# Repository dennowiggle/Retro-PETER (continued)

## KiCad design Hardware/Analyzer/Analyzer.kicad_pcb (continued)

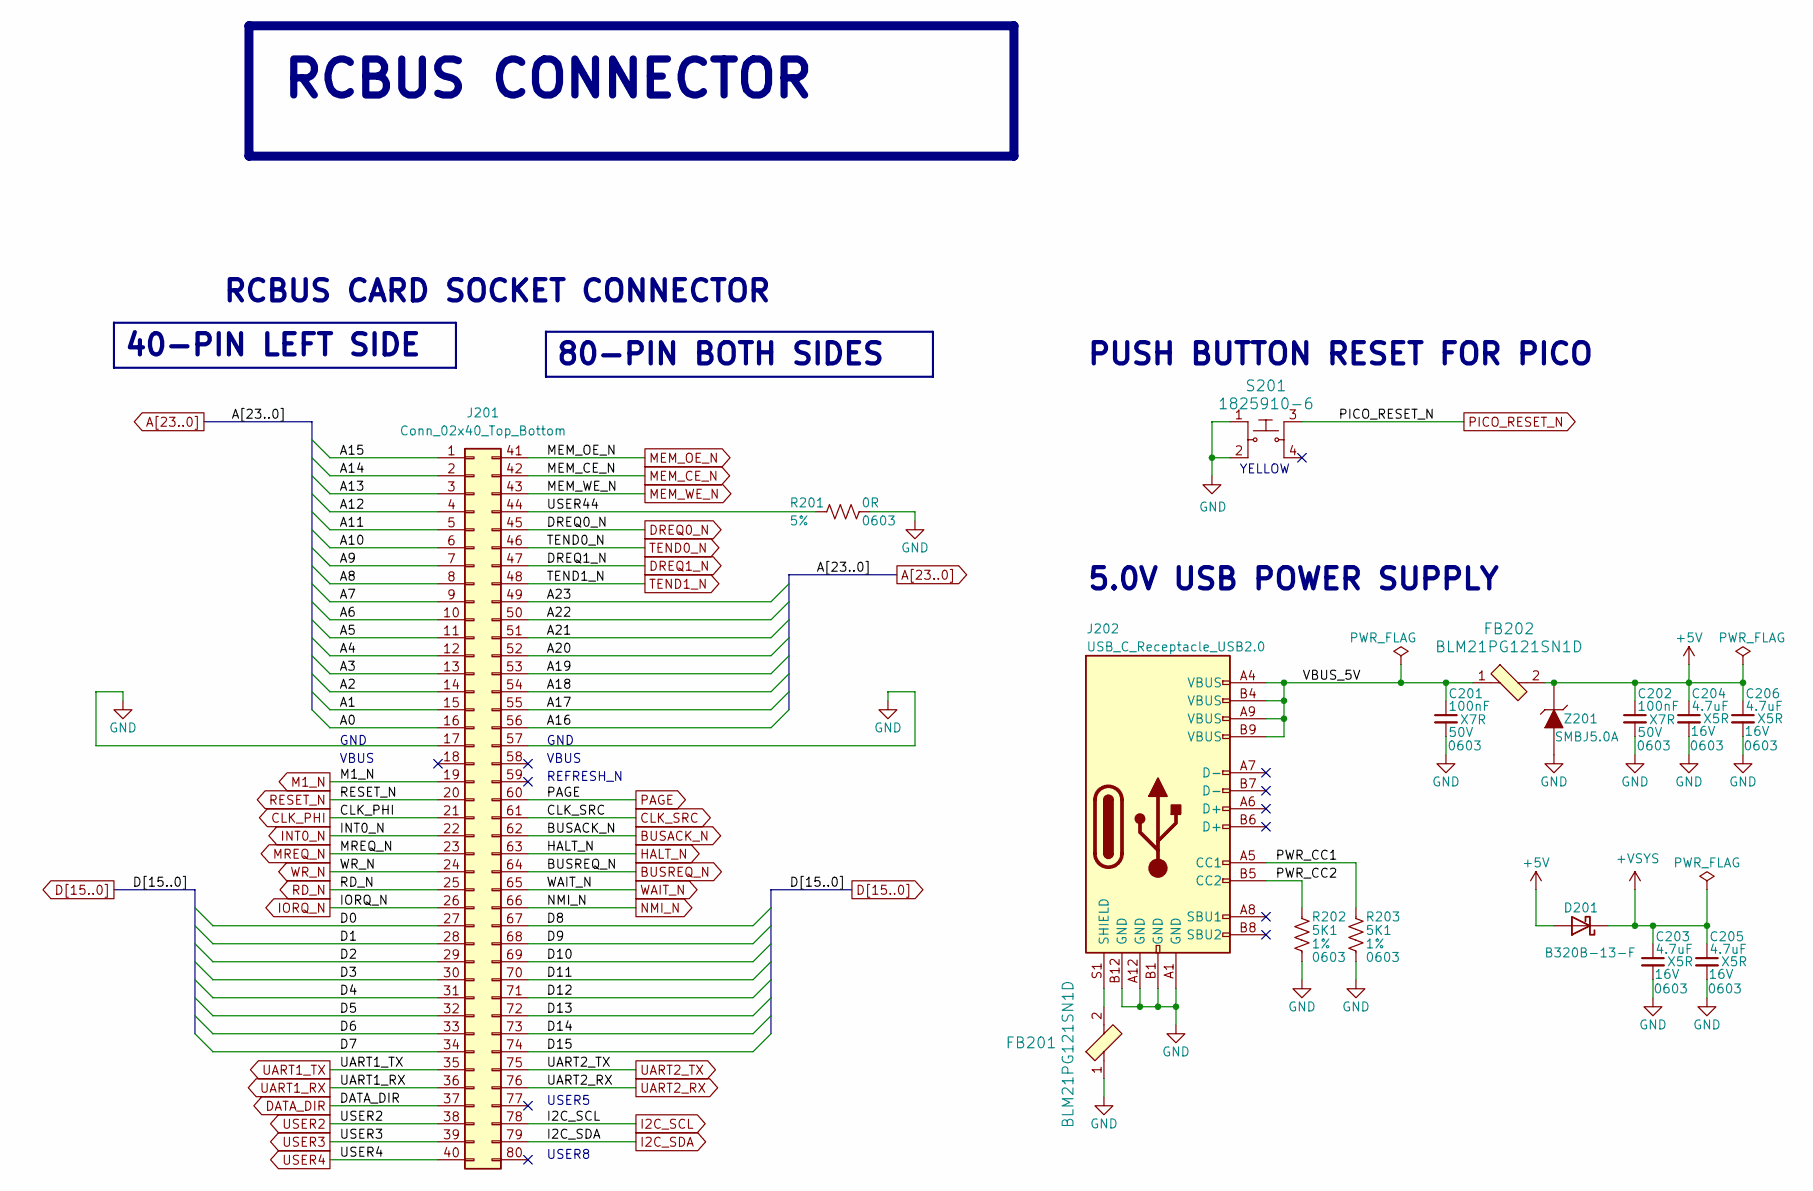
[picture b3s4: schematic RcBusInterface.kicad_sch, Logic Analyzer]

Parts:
C201, C202: 100nF; C_0603_1608Metric; Voltage 50V; Tolerance 10%; MPN CC0603KRX7R9BB104; Digikey 311-1344-1-ND
C203, C204, C205, C206: 4.7uF; C_0603_1608Metric; Voltage 16V; Tolerance 10%; MPN CL10A475KO8NNNC; Digikey 1276-1784-1-ND
D201: B320B-13-F; D_SMB; MPN B320B-13-F; Digikey B320B-FDICT-ND
FB201, FB202: BLM21PG121SN1D; L_0805_2012Metric; MPN BLM21PG121SN1D; Digikey 490-5986-1-ND
J201: Conn_02x40_Top_Bottom; RCBUS_PinHeader_2x40_P2.54mm_Horizontal; MPN PH2RA-80-UA; Digikey 2057-PH2RA-80-UA-ND
J202: USB_C_Receptacle_USB2.0; USB_C_Receptacle_HRO_TYPE-C-31-M-12; MPN USB4105-GF-A; LCSC Part # C167321
R201: 0R; R_0603_1608Metric; Tolerance 5%; MPN RC0603JR-070RL; Digikey 311-0.0GRCT-ND
R202, R203: 5K1; R_0603_1608Metric; Tolerance 1%; MPN RC0603FR-075K1L; Digikey 311-5.10KHRCT-ND
S201: 1825910-6; Switch_Tactile_THT_6x6mm; MPN 1825910-6; Digikey 450-1650-ND
Z201: SMBJ5.0A; D_SMB; MPN SMBJ5.0A; Digikey SMBJ5.0ALFCT-ND

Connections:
+5V: C202.1, C204.1, C206.1, D201.2 (A), FB202.2, Z201.1
+VSYS: C203.1, C205.1, D201.1 (K); also elsewhere on the board
/RcBusInterface/PWR_CC1: J202.A5 (CC1), R203.1
/RcBusInterface/PWR_CC2: J202.B5 (CC2), R202.1
/RcBusInterface/USER44: J201.44, R201.1
/RcBusInterface/VBUS_5V: C201.1, FB202.1, J202.A4 (VBUS), J202.A9 (VBUS), J202.B4 (VBUS), J202.B9 (VBUS)
A0: J201.16; also elsewhere on the board
A1: J201.15; also elsewhere on the board
A2: J201.14; also elsewhere on the board
A3: J201.13; also elsewhere on the board
A4: J201.12; also elsewhere on the board
A5: J201.11; also elsewhere on the board
A6: J201.10; also elsewhere on the board
A7: J201.9; also elsewhere on the board
A8: J201.8; also elsewhere on the board
A9: J201.7; also elsewhere on the board
A10: J201.6; also elsewhere on the board
A11: J201.5; also elsewhere on the board
A12: J201.4; also elsewhere on the board
A13: J201.3; also elsewhere on the board
A14: J201.2; also elsewhere on the board
A15: J201.1; also elsewhere on the board
A16: J201.56; also elsewhere on the board
A17: J201.55; also elsewhere on the board
A18: J201.54; also elsewhere on the board
A19: J201.53; also elsewhere on the board
A20: J201.52; also elsewhere on the board
A21: J201.51; also elsewhere on the board
A22: J201.50; also elsewhere on the board
A23: J201.49; also elsewhere on the board
BUSACK_N: J201.62; also elsewhere on the board
BUSREQ_N: J201.64; also elsewhere on the board
CLK_PHI: J201.21; also elsewhere on the board
CLK_SRC: J201.61; also elsewhere on the board
D0: J201.27; also elsewhere on the board
D1: J201.28; also elsewhere on the board
D2: J201.29; also elsewhere on the board
D3: J201.30; also elsewhere on the board
D4: J201.31; also elsewhere on the board
D5: J201.32; also elsewhere on the board
D6: J201.33; also elsewhere on the board
D7: J201.34; also elsewhere on the board
D8: J201.67; also elsewhere on the board
D9: J201.68; also elsewhere on the board
D10: J201.69; also elsewhere on the board
D11: J201.70; also elsewhere on the board
D12: J201.71; also elsewhere on the board
D13: J201.72; also elsewhere on the board
D14: J201.73; also elsewhere on the board
D15: J201.74; also elsewhere on the board
DATA_DIR: J201.37; also elsewhere on the board
DREQ0_N: J201.45; also elsewhere on the board
DREQ1_N: J201.47; also elsewhere on the board
GND: C201.2, C202.2, C203.2, C204.2, C205.2, C206.2, FB201.1, J201.17, J201.57, J202.A1 (GND), J202.A12 (GND), J202.B1 (GND), J202.B12 (GND), R201.2, R202.2, R203.2, S201.1, S201.2, Z201.2; also elsewhere on the board
HALT_N: J201.63; also elsewhere on the board
I2C_SCL: J201.78; also elsewhere on the board
I2C_SDA: J201.79; also elsewhere on the board
INT0_N: J201.22; also elsewhere on the board
IORQ_N: J201.26; also elsewhere on the board
M1_N: J201.19; also elsewhere on the board
MEM_CE_N: J201.42; also elsewhere on the board
MEM_OE_N: J201.41; also elsewhere on the board
MEM_WE_N: J201.43; also elsewhere on the board
MREQ_N: J201.23; also elsewhere on the board
NMI_N: J201.66; also elsewhere on the board
unnamed: FB201.2, J202.S1 (SHIELD)
PAGE: J201.60; also elsewhere on the board
PICO_RESET_N: S201.3; also elsewhere on the board
RD_N: J201.25; also elsewhere on the board
RESET_N: J201.20; also elsewhere on the board
TEND0_N: J201.46; also elsewhere on the board
TEND1_N: J201.48; also elsewhere on the board
UART1_RX: J201.36; also elsewhere on the board
UART1_TX: J201.35; also elsewhere on the board
UART2_RX: J201.76; also elsewhere on the board
UART2_TX: J201.75; also elsewhere on the board
USER2: J201.38; also elsewhere on the board
USER3: J201.39; also elsewhere on the board
USER4: J201.40; also elsewhere on the board
WAIT_N: J201.65; also elsewhere on the board
WR_N: J201.24; also elsewhere on the board

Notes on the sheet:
5.0V USB POWER SUPPLY
REFRESH_N
VBUS
40-PIN LEFT SIDE
USER8
80-PIN BOTH SIDES
YELLOW
GND
RCBUS CARD SOCKET CONNECTOR
PUSH BUTTON RESET FOR PICO
USER5
RCBUS CONNECTOR

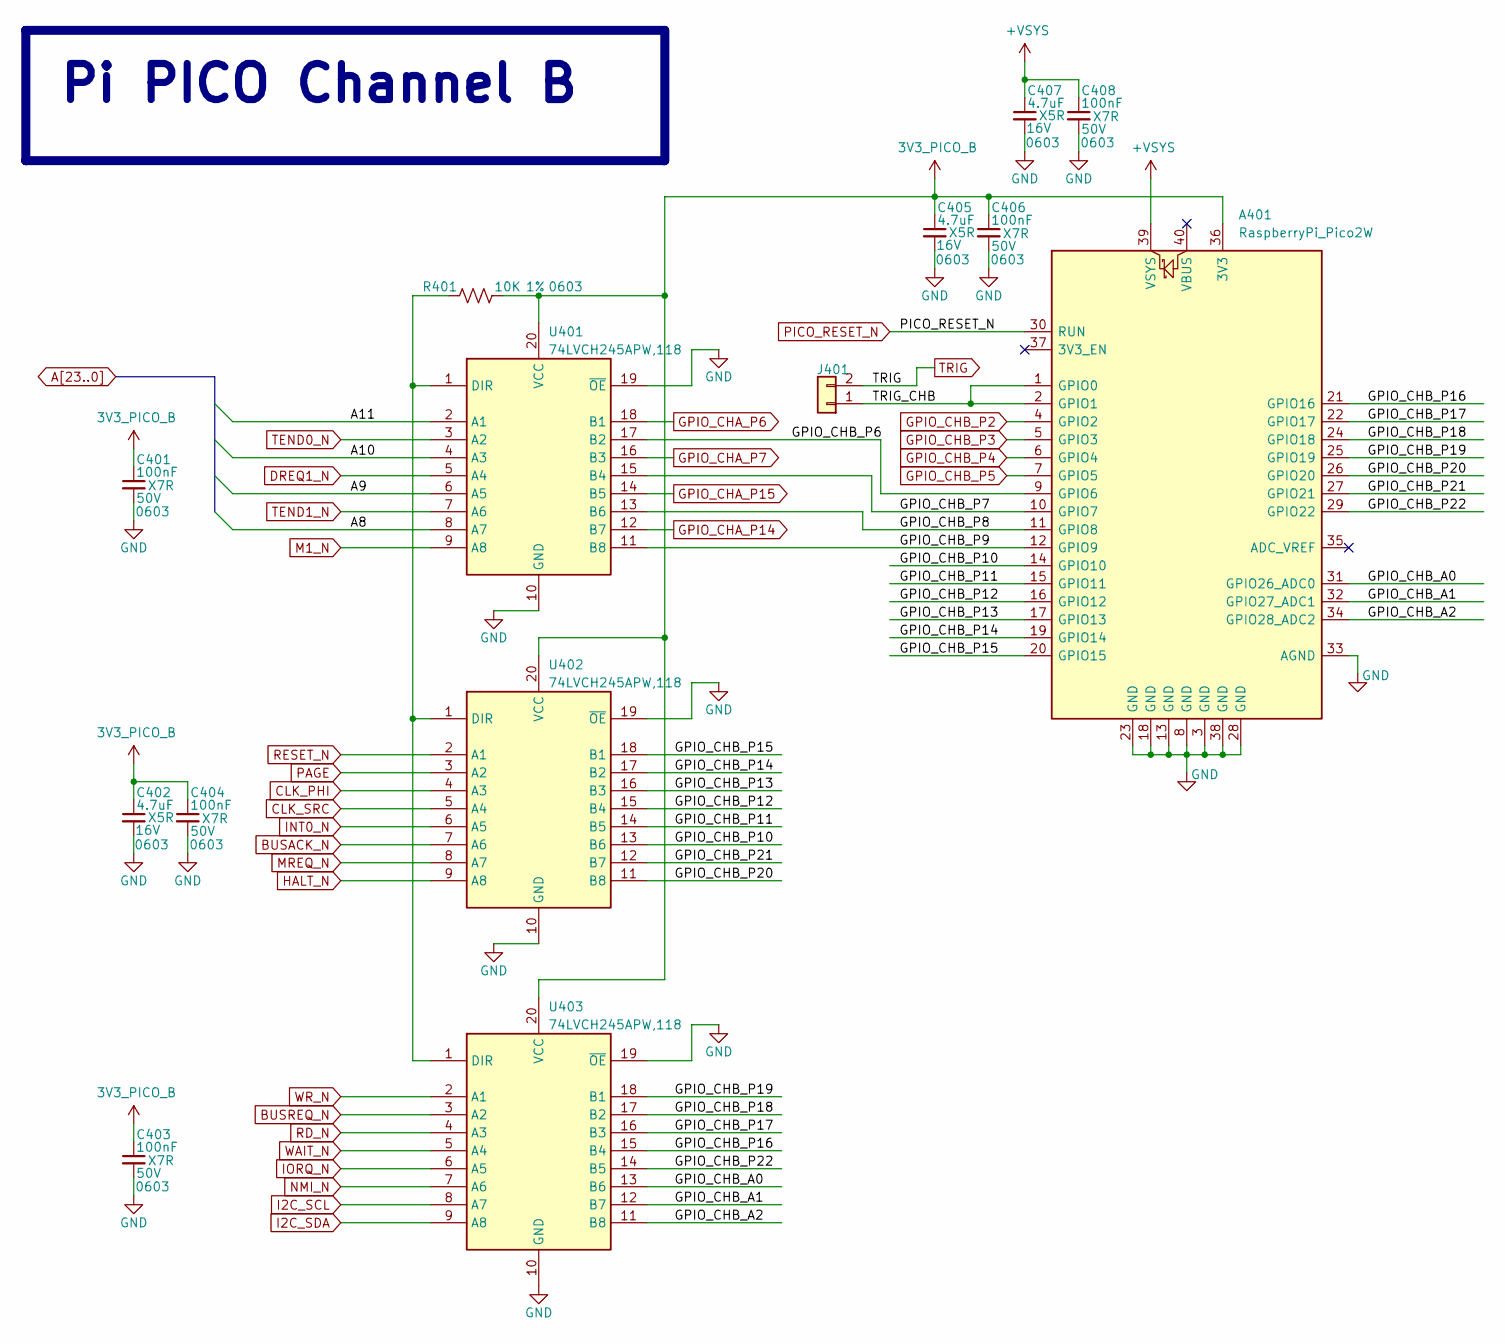
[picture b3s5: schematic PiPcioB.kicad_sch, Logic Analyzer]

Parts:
A401: RaspberryPi_Pico2W; RaspberryPi_Pico_Common_THT; MPN SC1634; Digikey 2648-SC1634-ND
C401, C403, C404, C406, C408: 100nF; C_0603_1608Metric; Voltage 50V; Tolerance 10%; MPN CC0603KRX7R9BB104; Digikey 311-1344-1-ND
C402, C405, C407: 4.7uF; C_0603_1608Metric; Voltage 16V; Tolerance 10%; MPN CL10A475KO8NNNC; Digikey 1276-1784-1-ND
J401: Conn_01x02; PinHeader_1x02_P2.54mm_Vertical; MPN PH2-02-UA; Digikey 2057-PH2-02-UA-ND
R401: 10K; R_0603_1608Metric; Tolerance 1%; MPN RC0603FR-0710KL; Digikey 311-10.0KHRCT-ND
U401, U402, U403: 74LVCH245APW,118; TSSOP-20_4.4x6.5mm_P0.65mm; MPN 74LVCH245APW,118; Digikey 1727-4041-1-ND

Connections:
3V3_PICO_B: A401.36 (3V3), C401.1, C402.1, C403.1, C404.1, C405.1, C406.1, R401.2, U401.20 (VCC), U402.20 (VCC), U403.20 (VCC)
+VSYS: A401.39 (VSYS), C407.1, C408.1; also elsewhere on the board
/PiPicoB/GPIO_CHB_A0: A401.31 (GPIO26_ADC0), U403.13 (B6)
/PiPicoB/GPIO_CHB_A1: A401.32 (GPIO27_ADC1), U403.12 (B7)
/PiPicoB/GPIO_CHB_A2: A401.34 (GPIO28_ADC2), U403.11 (B8)
/PiPicoB/GPIO_CHB_P6: A401.9 (GPIO6), U401.17 (B2)
/PiPicoB/GPIO_CHB_P7: A401.10 (GPIO7), U401.15 (B4)
/PiPicoB/GPIO_CHB_P8: A401.11 (GPIO8), U401.13 (B6)
/PiPicoB/GPIO_CHB_P9: A401.12 (GPIO9), U401.11 (B8)
/PiPicoB/GPIO_CHB_P10: A401.14 (GPIO10), U402.13 (B6)
/PiPicoB/GPIO_CHB_P11: A401.15 (GPIO11), U402.14 (B5)
/PiPicoB/GPIO_CHB_P12: A401.16 (GPIO12), U402.15 (B4)
/PiPicoB/GPIO_CHB_P13: A401.17 (GPIO13), U402.16 (B3)
/PiPicoB/GPIO_CHB_P14: A401.19 (GPIO14), U402.17 (B2)
/PiPicoB/GPIO_CHB_P15: A401.20 (GPIO15), U402.18 (B1)
/PiPicoB/GPIO_CHB_P16: A401.21 (GPIO16), U403.15 (B4)
/PiPicoB/GPIO_CHB_P17: A401.22 (GPIO17), U403.16 (B3)
/PiPicoB/GPIO_CHB_P18: A401.24 (GPIO18), U403.17 (B2)
/PiPicoB/GPIO_CHB_P19: A401.25 (GPIO19), U403.18 (B1)
/PiPicoB/GPIO_CHB_P20: A401.26 (GPIO20), U402.11 (B8)
/PiPicoB/GPIO_CHB_P21: A401.27 (GPIO21), U402.12 (B7)
/PiPicoB/GPIO_CHB_P22: A401.29 (GPIO22), U403.14 (B5)
/PiPicoB/TRIG_CHB: A401.1 (GPIO0), A401.2 (GPIO1), J401.1
A8: U401.8 (A7); also elsewhere on the board
A9: U401.6 (A5); also elsewhere on the board
A10: U401.4 (A3); also elsewhere on the board
A11: U401.2 (A1); also elsewhere on the board
BUSACK_N: U402.7 (A6); also elsewhere on the board
BUSREQ_N: U403.3 (A2); also elsewhere on the board
CLK_PHI: U402.4 (A3); also elsewhere on the board
CLK_SRC: U402.5 (A4); also elsewhere on the board
DREQ1_N: U401.5 (A4); also elsewhere on the board
GND: A401.3 (GND), A401.8 (GND), A401.13 (GND), A401.18 (GND), A401.23 (GND), A401.28 (GND), A401.33 (AGND), A401.38 (GND), C401.2, C402.2, C403.2, C404.2, C405.2, C406.2, C407.2, C408.2, U401.10 (GND), U401.19 (~OE), U402.10 (GND), U402.19 (~OE), U403.10 (GND), U403.19 (~OE); also elsewhere on the board
GPIO_CHA_P6: U401.18 (B1); also elsewhere on the board
GPIO_CHA_P7: U401.16 (B3); also elsewhere on the board
GPIO_CHA_P14: U401.12 (B7); also elsewhere on the board
GPIO_CHA_P15: U401.14 (B5); also elsewhere on the board
GPIO_CHB_P2: A401.4 (GPIO2); also elsewhere on the board
GPIO_CHB_P3: A401.5 (GPIO3); also elsewhere on the board
GPIO_CHB_P4: A401.6 (GPIO4); also elsewhere on the board
GPIO_CHB_P5: A401.7 (GPIO5); also elsewhere on the board
HALT_N: U402.9 (A8); also elsewhere on the board
I2C_SCL: U403.8 (A7); also elsewhere on the board
I2C_SDA: U403.9 (A8); also elsewhere on the board
INT0_N: U402.6 (A5); also elsewhere on the board
IORQ_N: U403.6 (A5); also elsewhere on the board
M1_N: U401.9 (A8); also elsewhere on the board
MREQ_N: U402.8 (A7); also elsewhere on the board
NMI_N: U403.7 (A6); also elsewhere on the board
unnamed: R401.1, U401.1 (DIR), U402.1 (DIR), U403.1 (DIR)
PAGE: U402.3 (A2); also elsewhere on the board
PICO_RESET_N: A401.30 (RUN); also elsewhere on the board
RD_N: U403.4 (A3); also elsewhere on the board
RESET_N: U402.2 (A1); also elsewhere on the board
TEND0_N: U401.3 (A2); also elsewhere on the board
TEND1_N: U401.7 (A6); also elsewhere on the board
TRIG: J401.2; also elsewhere on the board
WAIT_N: U403.5 (A4); also elsewhere on the board
WR_N: U403.2 (A1); also elsewhere on the board

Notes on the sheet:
Pi PICO Channel B

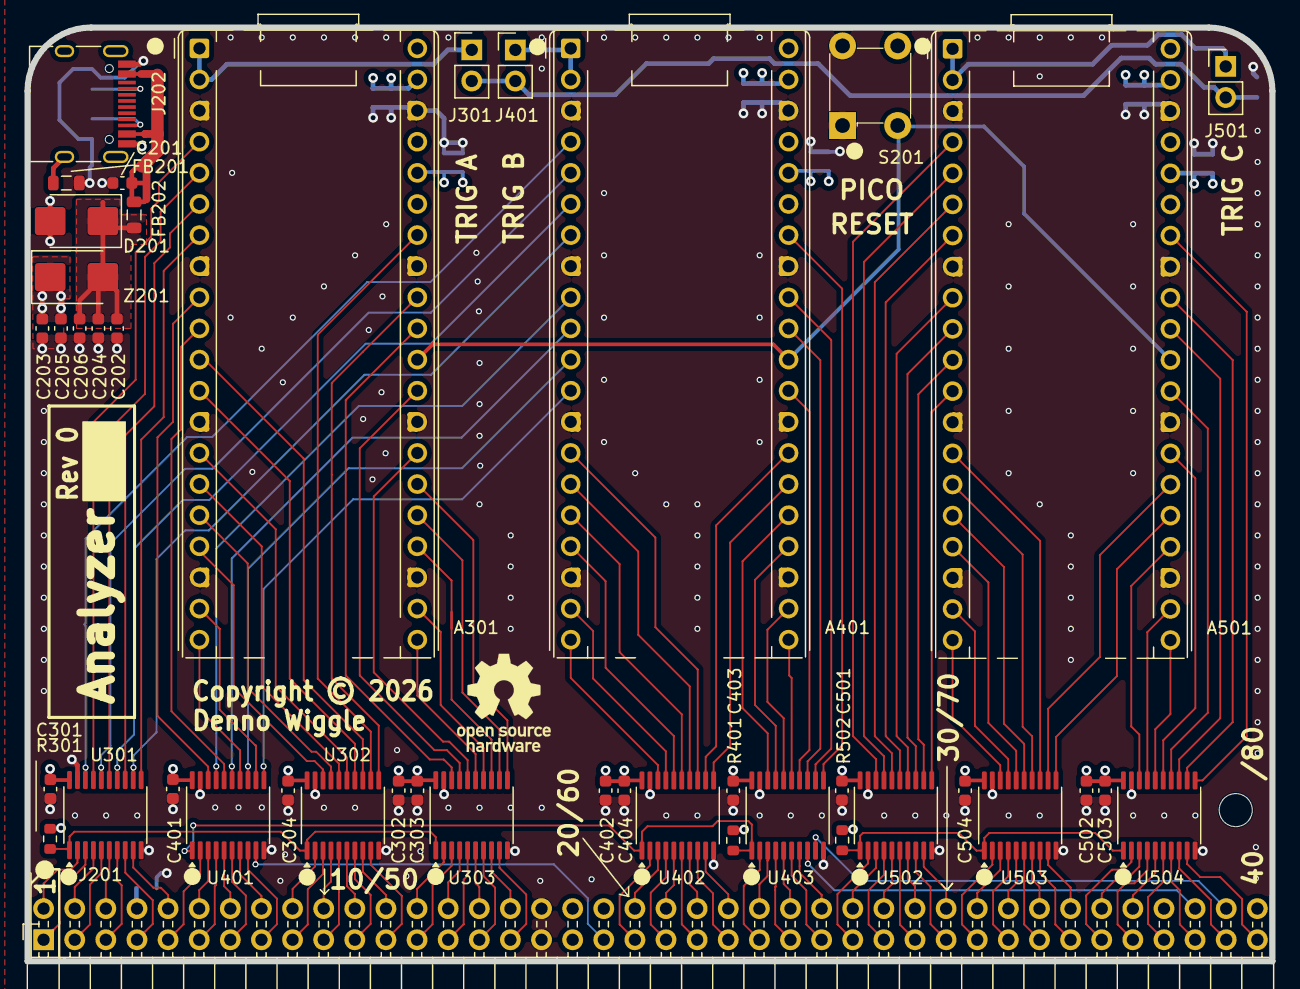
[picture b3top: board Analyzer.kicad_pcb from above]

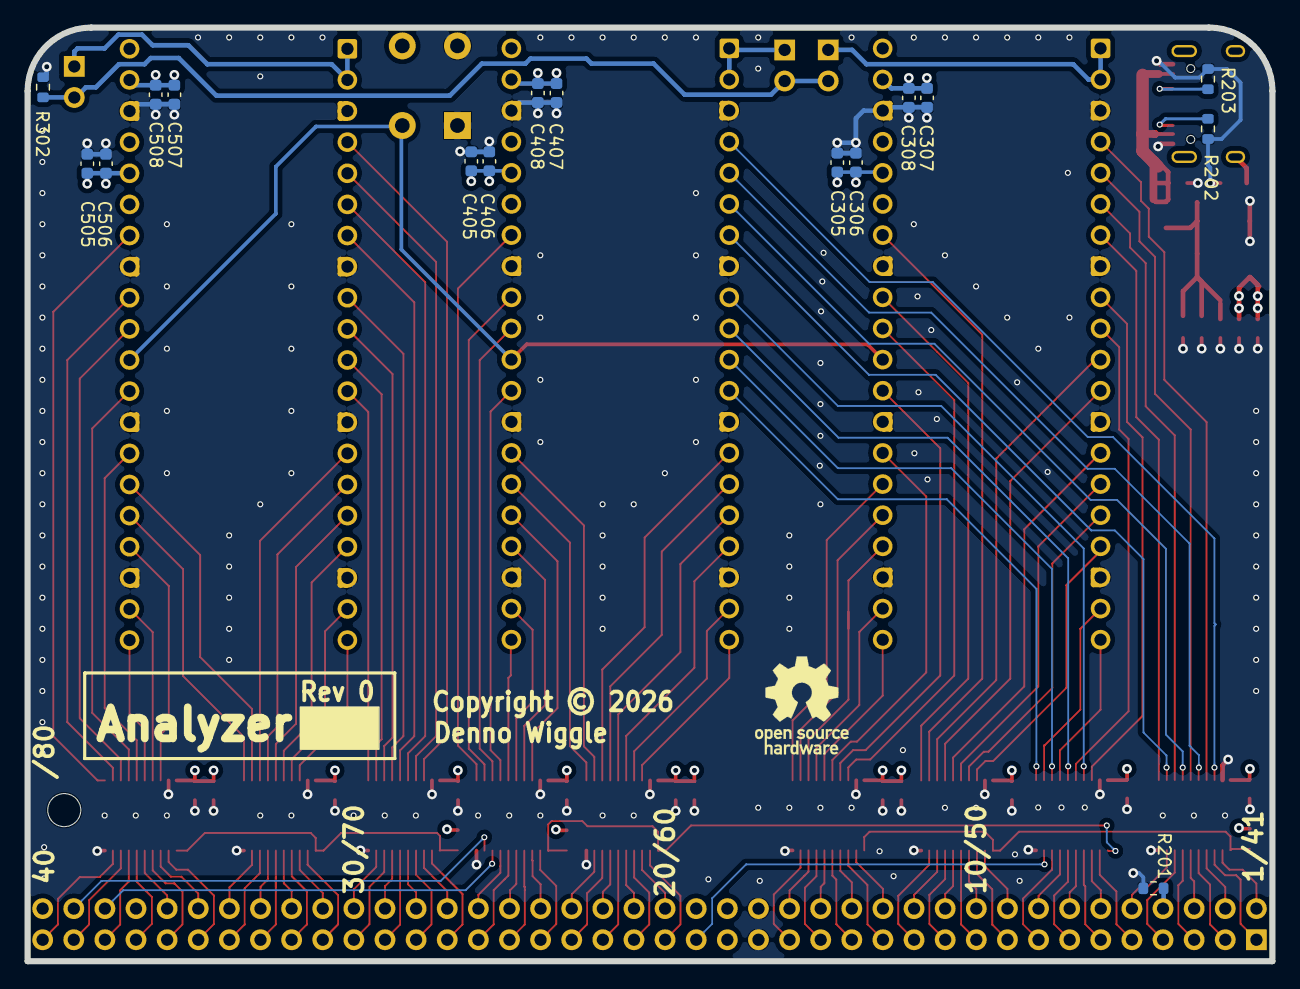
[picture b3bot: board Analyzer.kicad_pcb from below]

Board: 4 copper layers, 101.6 x 76.2 mm, 62 parts (17 on the bottom side), 163 nets.

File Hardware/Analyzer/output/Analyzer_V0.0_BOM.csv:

"Reference","Value","Footprint","Qty","DNP","Digikey","LCSC Part #","MPN","Manufacturer","Description"
"Z201","SMBJ5.0A","Diode_SMD:D_SMB","1","","SMBJ5.0ALFCT-ND","C110528","SMBJ5.0A","Littlefuse","TVS DIODE 5VWM 9.2VC DO214AA"
"U301,U302,U303,U401,U402,U403,U502,U503,U504","74LVCH245APW,118","Package_SO:TSSOP-20_4.4x6.5mm_P0.65mm","9","","1727-4041-1-ND","C426764","74LVCH245APW,118","Nexperia USA Inc.","IC TXRX NON-INVERT 3.6V 20-TSSOP"
"S201","1825910-6","digikey-footprints:Switch_Tactile_THT_6x6mm","1","","450-1650-ND","","1825910-6","TE Connectivity ALCOSWITCH Switches","SWITCH TACTILE SPST-NO 0.05A 24V"
"R302","2.2K","Resistor_SMD:R_0603_1608Metric","1","","311-2.20KHRCT-ND","C114662","RC0603FR-072K2L","Yaego","RES 2.2K OHM 1% 1/10W 0603"
"R301,R401,R502","10K","Resistor_SMD:R_0603_1608Metric","3","","311-10.0KHRCT-ND","C98220","RC0603FR-0710KL","Yaego","RES 10K OHM 1% 1/10W 0603"
"R202,R203","5K1","Resistor_SMD:R_0603_1608Metric","2","","311-5.10KHRCT-ND","C105580","RC0603FR-075K1L","Yaego","RES 5.1K OHM 1% 1/10W 0603"
"R201","0R","Resistor_SMD:R_0603_1608Metric","1","","311-0.0GRCT-ND","C95177","RC0603JR-070RL","Yaego","RES 0 OHM 5% 1/10W 0603"
"J301,J401,J501","Conn_01x02","Connector_PinHeader_2.54mm:PinHeader_1x02_P2.54mm_Vertical","3","","2057-PH2-02-UA-ND","","PH2-02-UA","Adam Tech","CONN HEADER VERT 2POS 2.54MM"
"J202","USB_C_Receptacle_USB2.0","WTM_Library:USB_C_Receptacle_HRO_TYPE-C-31-M-12","1","","2073-USB4105-GF-ACT-ND","C167321","USB4105-GF-A","GCT","CONN RCP USB2.0 TYP C 24P SMD RA"
"J201","Conn_02x40_Top_Bottom","WTM_Library:RCBUS_PinHeader_2x40_P2.54mm_Horizontal","1","","2057-PH2RA-80-UA-ND","","PH2RA-80-UA","Adam Tech","CONN HEADER R/A 80POS 2.54MM"
"H4","MountingHole","MountingHole:MountingHole_2.7mm_M2.5_DIN965","1","","","","","",""
"FB201,FB202","BLM21PG121SN1D","Inductor_SMD:L_0805_2012Metric","2","","490-5986-1-ND","C79382","BLM21PG121SN1D","Murata Electronics North America","FERRITE BEAD 120 OHM 0805 3A"
"D201","B320B-13-F","Diode_SMD:D_SMB","1","","B320B-FDICT-ND","C134449","B320B-13-F","Diodes Inc","DIODE SCHOTTKY 20V 3A SMB"
"C203,C204,C205,C206,C302,C305,C307,C402,C405,C407,C502,C505,C507","4.7uF","Capacitor_SMD:C_0603_1608Metric","13","","1276-1784-1-ND","C19666","CL10A475KO8NNNC","Yaego","CAP CER 4.7UF 16V X5R 0603"
"C201,C202,C301,C303,C304,C306,C308,C401,C403,C404,C406,C408,C501,C503,C504,C506,C508","100nF","Capacitor_SMD:C_0603_1608Metric","17","","311-1344-1-ND","C14663","CC0603KRX7R9BB104","YAGEO","CAP CER 0.1UF 50V X7R 0603"
"A301,A401,A501","RaspberryPi_Pico2W","Module:RaspberryPi_Pico_Common_THT","3","","2648-SC1634-ND","","SC1634","Raspberry Pi","RASPBERRY PI PICO 2 WH RP2350"

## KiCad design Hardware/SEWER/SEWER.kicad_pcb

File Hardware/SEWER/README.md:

# SEWER
Simple Eval With EZ80F91 on RCBUS

## Description
SEWER is an RCBUS board with an ez80F91 CPU. There is no RAM or ROM memory hosted on the board.

## Top View

## Bottom View

## SEWER Board Rev 0.0 Release Notes

1. The 'output' directory contains the BOM, netlist, and PDF schematic.

2. Board design used KiCad 8.0.4.

3. This board was designed for evaluation purposes. It is not a final design.

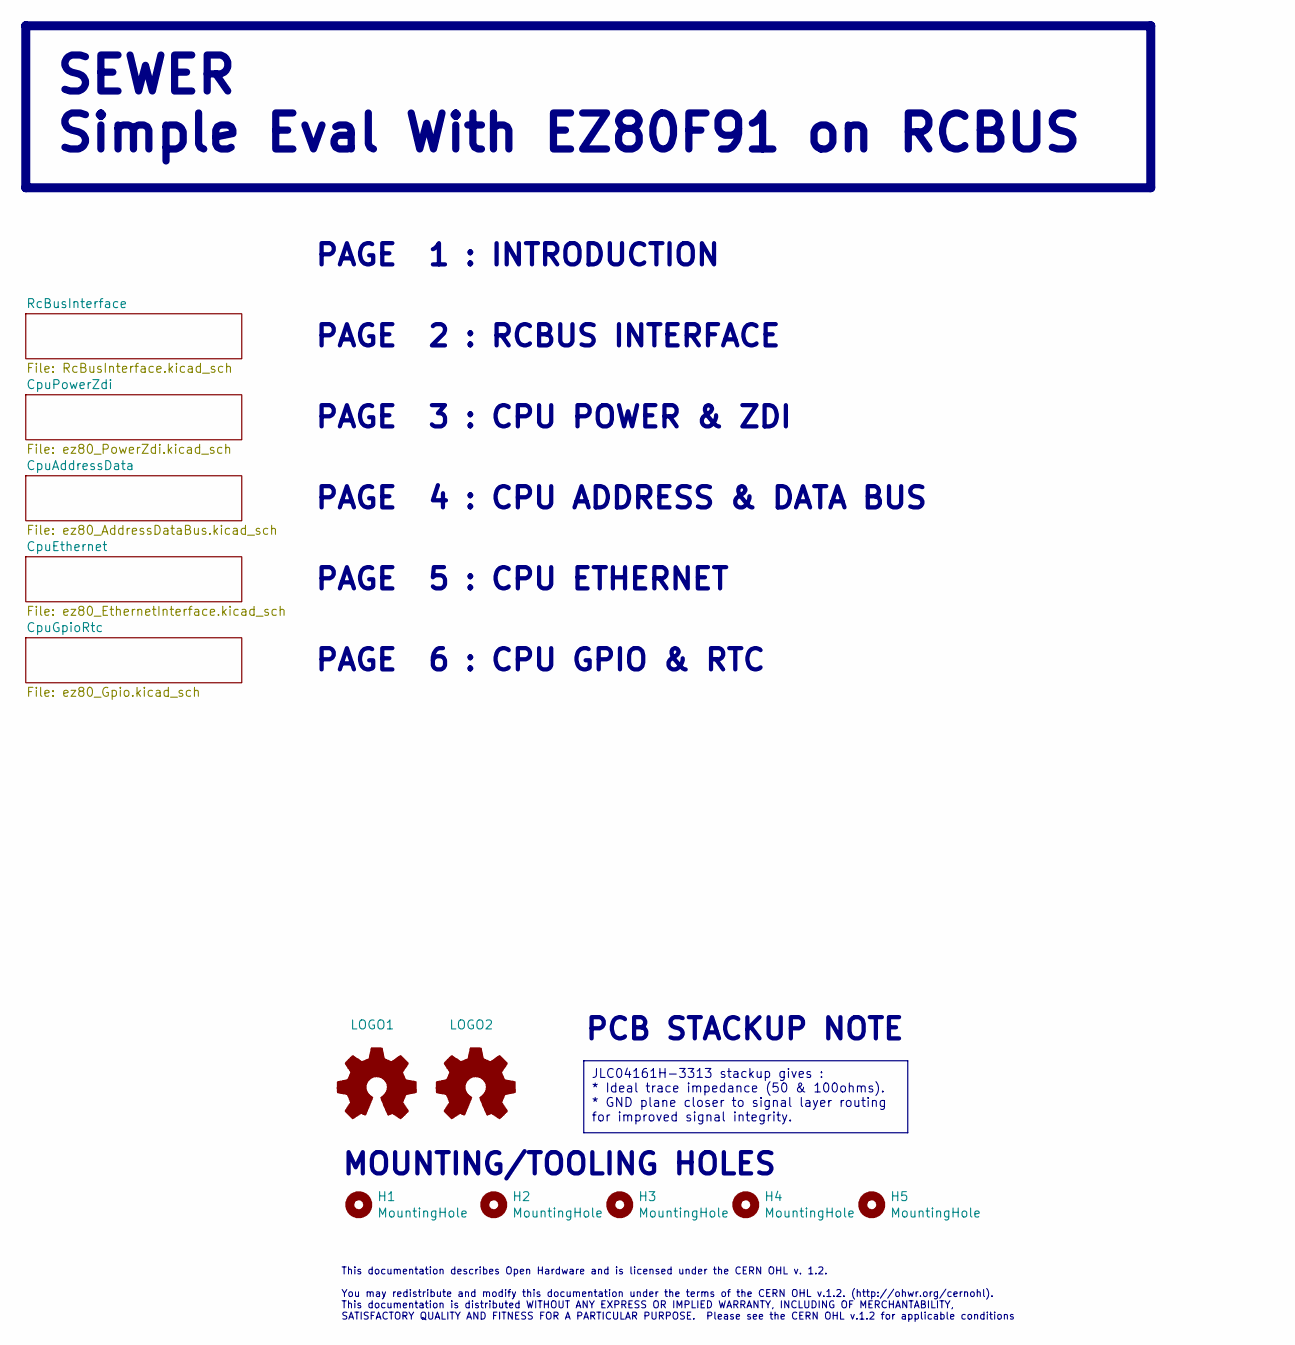
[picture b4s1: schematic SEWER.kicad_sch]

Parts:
H1: MountingHole; MountingHole_3.2mm_M3
H2, H3, H4, H5: MountingHole; MountingHole_2.7mm_M2.5_DIN965
LOGO1, LOGO2: Logo_Open_Hardware_Small; OSHW-Logo_7.5x8mm_SilkScreen

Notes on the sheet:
JLC04161H-3313 stackup gives : * Ideal trace impedance (50 & 100ohms). * GND plane closer to signal layer routing for improved signal integrity.
SEWER Simple Eval With EZ80F91 on RCBUS
PAGE 5 : CPU ETHERNET
PAGE 1 : INTRODUCTION
PAGE 4 : CPU ADDRESS & DATA BUS
PAGE 2 : RCBUS INTERFACE
MOUNTING/TOOLING HOLES
This documentation describes Open Hardware and is licensed under the CERN OHL v. 1.2. You may redistribute and modify this documentation under the terms of the CERN OHL v.1.2. (http://ohwr.org/cernohl). This documentation is distributed WITHOUT ANY EXPRESS OR IMPLIED WARRANTY, INCLUDING OF MERCHANT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
PAGE 6 : CPU GPIO & RTC
PAGE 3 : CPU POWER & ZDI
PCB STACKUP NOTE

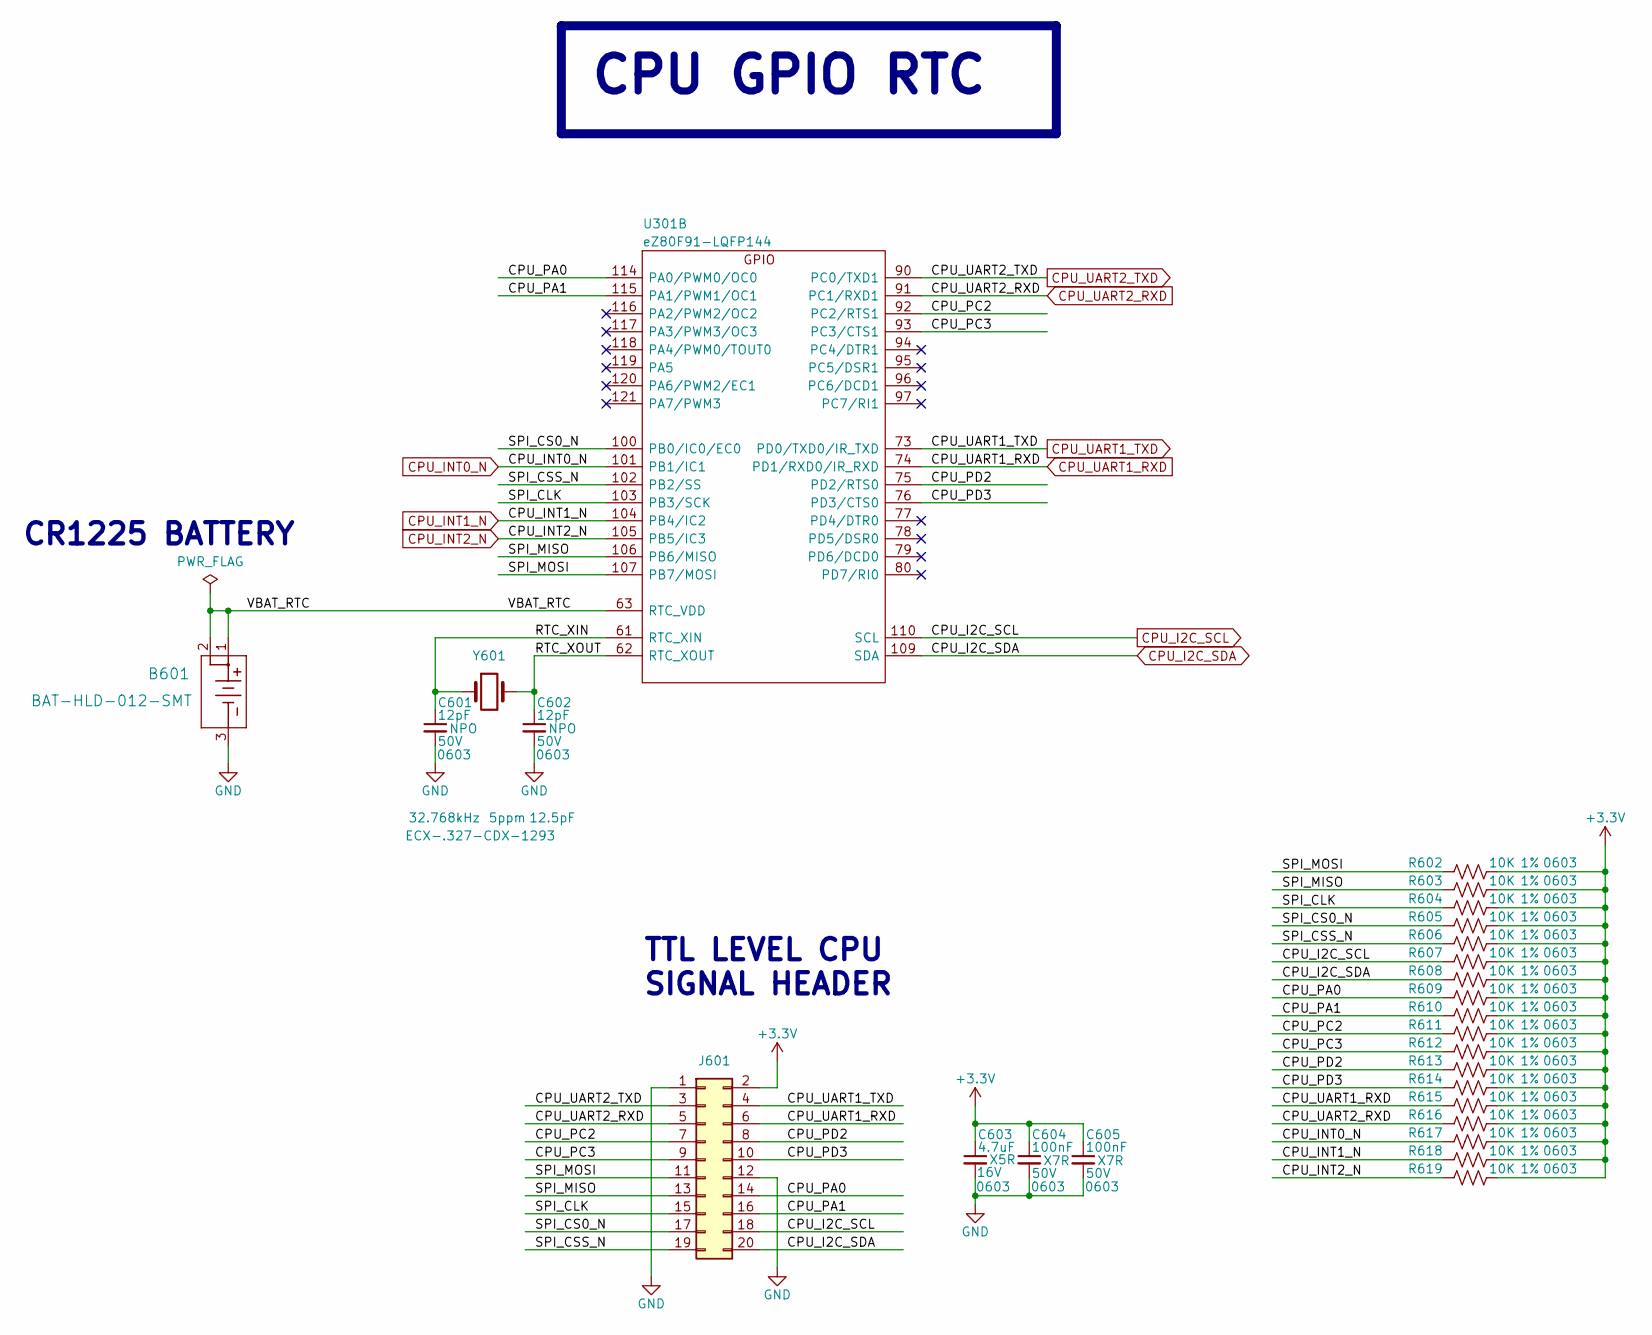
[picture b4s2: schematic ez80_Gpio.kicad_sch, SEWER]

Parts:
B601: BAT-HLD-012-SMT; BAT-HLD-012-SMT_TEC; MPN BAT-HLD-012-SMT; Digikey BAT-HLD-012-SMT-ND
C601, C602: 12pF; C_0603_1608Metric; Voltage 50V; Tolerance 5%; MPN CL10C120JB8NNNC; Digikey 1276-1254-1-ND
C603: 4.7uF; C_0603_1608Metric; Voltage 16V; Tolerance 10%; MPN CL10A475KO8NNNC; Digikey 1276-1784-1-ND
C604, C605: 100nF; C_0603_1608Metric; Voltage 50V; Tolerance 10%; MPN CC0603KRX7R9BB104; Digikey 311-1344-1-ND
J601: Conn_02x10_Odd_Even; PinHeader_2x10_P2.54mm_Horizontal; MPN PH2RA-20-UA; Digikey 2057-PH2RA-20-UA-ND
R602, R603, R604, R605, R606, R607, R608, R609, R610, R611, R612, R613, R614, R615, R616, R617, R618, R619: 10K; R_0603_1608Metric; Tolerance 1%; MPN RC0603FR-0710KL; Digikey 311-10.0KHRCT-ND
U301: eZ80F91-LQFP144; LQFP-144_20x20mm_P0.5mm; MPN EZ80F91AZA50EK; Digikey 269-EZ80F91AZA50EK-ND
Y601: ECX-.327-CDX-1293; Crystal_SMD_EuroQuartz_EQ161-2Pin_3.2x1.5mm_HandSoldering; Tolerance 5ppm; MPN ECX-.327-CDX-1293; Digikey XC2292CT-ND

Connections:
+3.3V: C603.1, C604.1, C605.1, J601.2, R602.2, R603.2, R604.2, R605.2, R606.2, R607.2, R608.2, R609.2, R610.2, R611.2, R612.2, R613.2, R614.2, R615.2, R616.2, R617.2, R618.2, R619.2; also elsewhere on the board
/CpuGpioRtc/CPU_PA0: J601.14, R609.1, U301.114 (PA0/PWM0/OC0)
/CpuGpioRtc/CPU_PA1: J601.16, R610.1, U301.115 (PA1/PWM1/OC1)
/CpuGpioRtc/CPU_PC2: J601.7, R611.1, U301.92 (PC2/RTS1)
/CpuGpioRtc/CPU_PC3: J601.9, R612.1, U301.93 (PC3/CTS1)
/CpuGpioRtc/CPU_PD2: J601.8, R613.1, U301.75 (PD2/RTS0)
/CpuGpioRtc/CPU_PD3: J601.10, R614.1, U301.76 (PD3/CTS0)
/CpuGpioRtc/RTC_XIN: C601.1, U301.61 (RTC_XIN), Y601.1
/CpuGpioRtc/RTC_XOUT: C602.1, U301.62 (RTC_XOUT), Y601.2
/CpuGpioRtc/SPI_CLK: J601.15, R604.1, U301.103 (PB3/SCK)
/CpuGpioRtc/SPI_CS0_N: J601.17, R605.1, U301.100 (PB0/IC0/EC0)
/CpuGpioRtc/SPI_CSS_N: J601.19, R606.1, U301.102 (PB2/SS)
/CpuGpioRtc/SPI_MISO: J601.13, R603.1, U301.106 (PB6/MISO)
/CpuGpioRtc/SPI_MOSI: J601.11, R602.1, U301.107 (PB7/MOSI)
/CpuGpioRtc/VBAT_RTC: B601.1, B601.2, U301.63 (RTC_VDD)
CPU_I2C_SCL: J601.18, R607.1, U301.110 (SCL); also elsewhere on the board
CPU_I2C_SDA: J601.20, R608.1, U301.109 (SDA); also elsewhere on the board
CPU_INT0_N: R617.1, U301.101 (PB1/IC1); also elsewhere on the board
CPU_INT1_N: R618.1, U301.104 (PB4/IC2); also elsewhere on the board
CPU_INT2_N: R619.1, U301.105 (PB5/IC3); also elsewhere on the board
CPU_UART1_RXD: J601.6, R615.1, U301.74 (PD1/RXD0/IR_RXD); also elsewhere on the board
CPU_UART1_TXD: J601.4, U301.73 (PD0/TXD0/IR_TXD); also elsewhere on the board
CPU_UART2_RXD: J601.5, R616.1, U301.91 (PC1/RXD1); also elsewhere on the board
CPU_UART2_TXD: J601.3, U301.90 (PC0/TXD1); also elsewhere on the board
GND: B601.3, C601.2, C602.2, C603.2, C604.2, C605.2, J601.1, J601.12; also elsewhere on the board

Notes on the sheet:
CPU GPIO RTC
CR1225 BATTERY
TTL LEVEL CPU SIGNAL HEADER
